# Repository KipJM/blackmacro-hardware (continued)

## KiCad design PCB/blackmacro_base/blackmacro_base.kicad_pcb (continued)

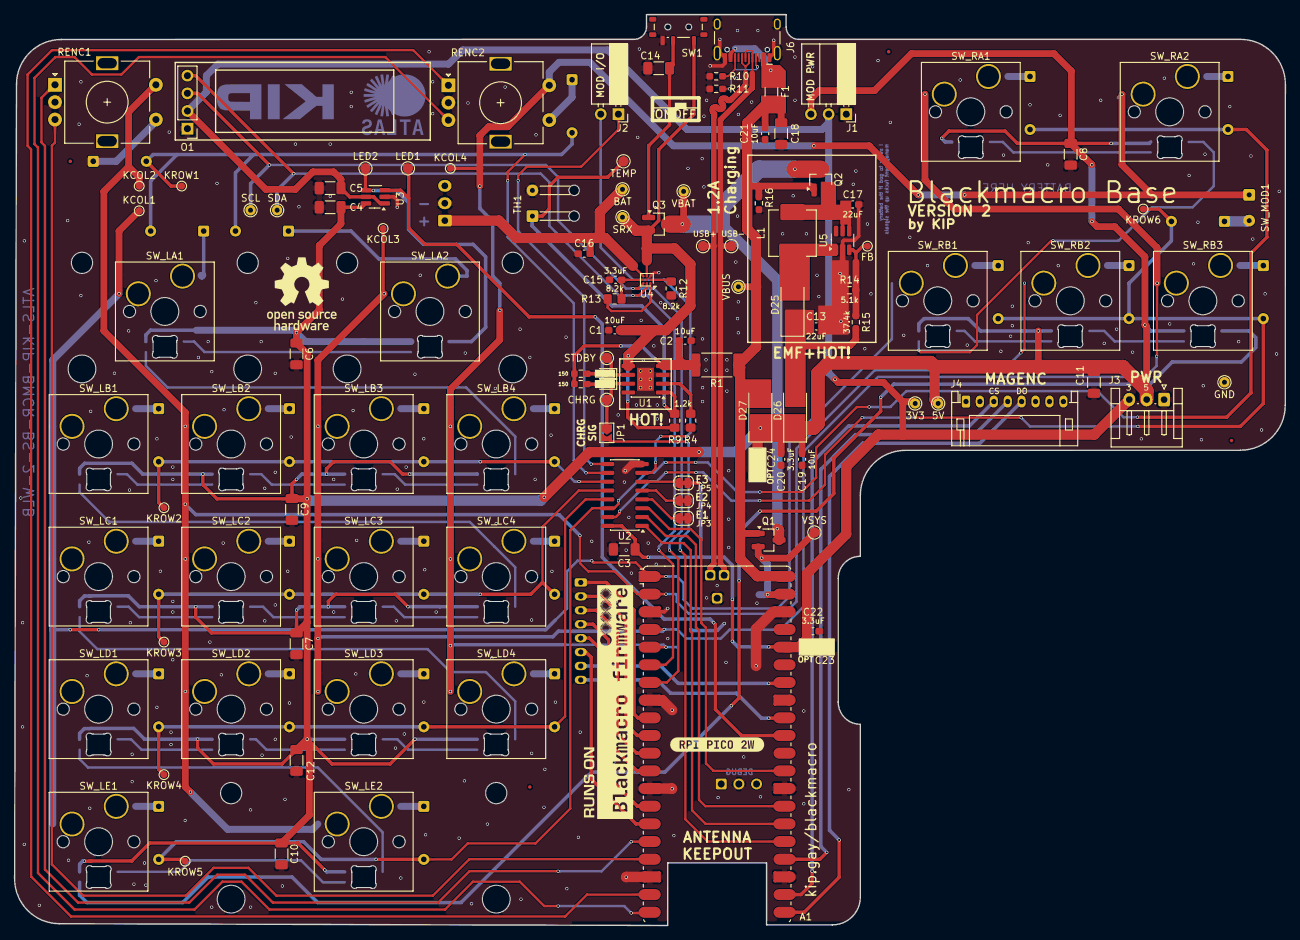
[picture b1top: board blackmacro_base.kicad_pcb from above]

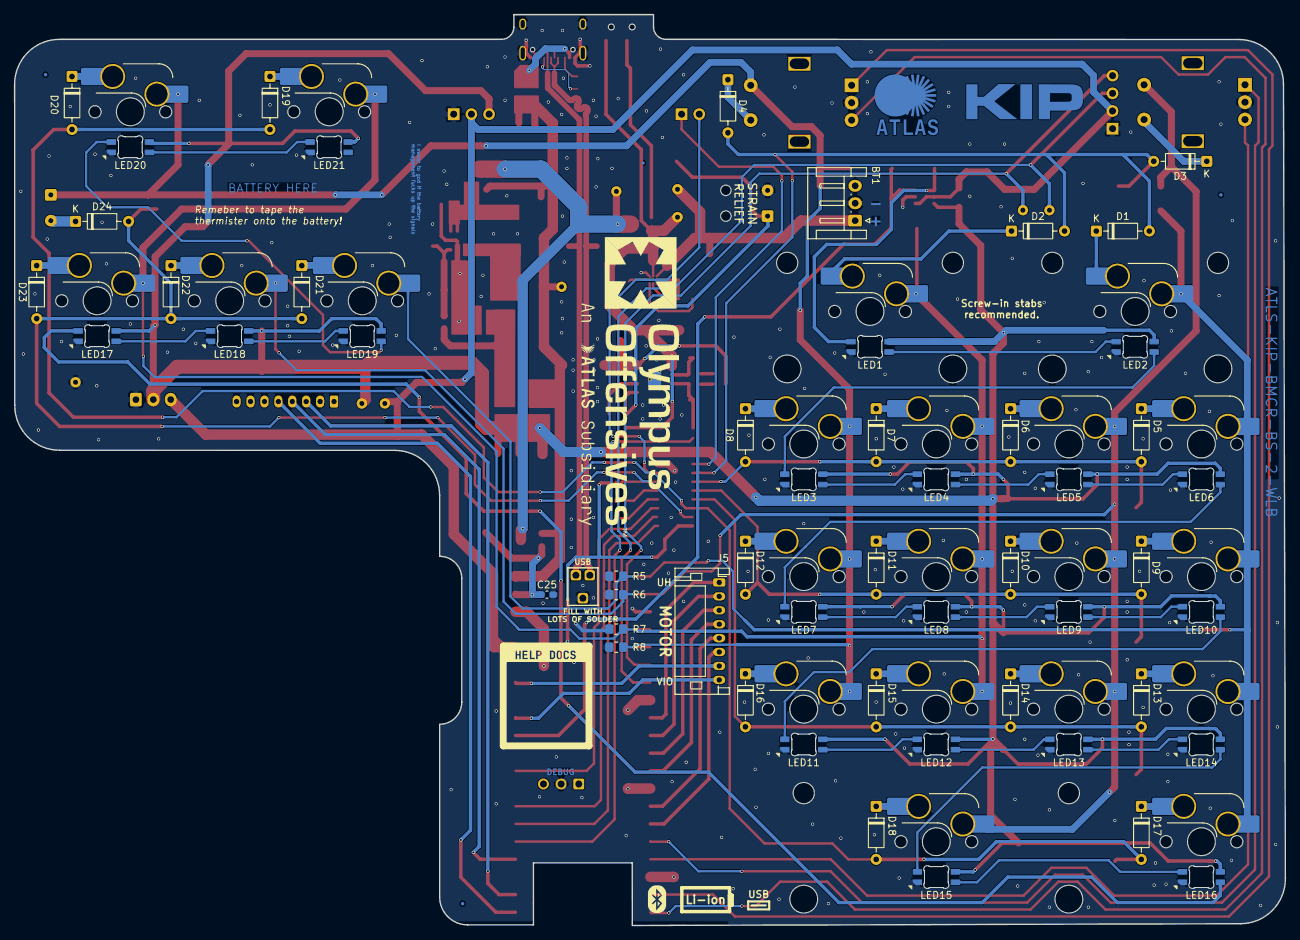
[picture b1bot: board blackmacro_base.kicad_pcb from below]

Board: 2 copper layers, 182.6 x 130.9 mm, 173 parts (53 on the bottom side), 110 nets.

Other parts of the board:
kibuzzard-6A2FA9C2: G***; kibuzzard-6A2FA9C2
kibuzzard-6A574CAA: G***; kibuzzard-6A574CAA

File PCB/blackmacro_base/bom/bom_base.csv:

,References,Value,Footprint,Quantity,Part,Link,Actual Total Cost (CNY)
1,"C3, C4, C5, C6, C7, C8, C9, C10, C11, C12",0.1uF,C_1206_3216Metric_Pad1.33x1.80mm_HandSolder,10,CL31B104KBCNNNC,https://item.szlcsc.com/25237.html,- (SEE DIAL BOM)
2,"R5, R6, R7, R8",8.2k,R_0805_2012Metric_Pad1.20x1.40mm_HandSolder,4,0805W8F8201T5E,https://item.szlcsc.com/18516.html,1.44
3,"D1, D2, D3, D4, D5, D6, D7, D8, D9, D10, D11, D12, D13, D14, D15, D16, D17, D18, D19, D20, D21, D22, D23, D24",1N4148WS,D_DO-35_SOD27_P7.62mm_Horizontal,24,1N4148WS THT,N/A,N/A (from inventory)
4,U2,74HC238,SOIC-16_3.9x9.9mm_P1.27mm,1,"74HC238D,653",https://item.szlcsc.com/6071.html,3.67
5,U3,SN74LVC1T45DBV,SOT-23-6_Handsoldering,1,SN74LVC1T45DBVR,https://item.szlcsc.com/8320.html,2.5
6,A1,RaspberryPi_Pico_W,RaspberryPi_Pico_W_SMD_HandSolder,1,LOBOROBO pico 2W Type-C clone board ,N/A (MUST BE TYPE-C!) (a lot of vendors resell this same exact board),46
7,"LED1, LED2, LED3, LED4, LED5, LED6, LED7, LED8, LED9, LED10, LED11, LED12, LED13, LED14, LED15, LED16, LED17, LED18, LED19, LED20, LED21",SK6812MINI-E,LED_MX_6028R,21,SK6812MINI-E,https://item.szlcsc.com/5773397.html,2.69
8,"SW_LB1, SW_LB2, SW_LB3, SW_LB4, SW_LC1, SW_LC2, SW_LC3, SW_LC4, SW_LD1, SW_LD2, SW_LD3, SW_LD4, SW_LE1, SW_RB1, SW_RB2, SW_RB3",SW_Push_45deg,SW_Hotswap_Kailh_MX_Plated_1.00u,16,CPG151101S11-16,https://item.szlcsc.com/43288200.html,8.22
9,"TP_KCOL1, TP_KCOL2, TP_KCOL3, TP_KCOL4, TP_KROW1, TP_KROW2, TP_KROW3, TP_KROW4, TP_KROW5, TP_KROW6, TP_LED1, TP_LED2",TestPoint,TestPoint_THTPad_D1.5mm_Drill0.7mm,12,N/A,N/A,
10,"TP_3V1, TP_GND1, TP_VBUS1",VSYS test point,TestPoint_THTPad_D1.5mm_Drill0.7mm,3,N/A,N/A,
11,"RENC1, RENC2",RotaryEncoder_Switch,RotaryEncoder_Alps_EC11E-Switch_Vertical_H20mm,2,(from inventory) By personal preference. EC11 rotary encoder with click input,N/A,N/A (from inventory)
12,"ST_LA1, ST_LA2",2u,STAB_MX_2u,2,screw-in 2u stabilizers (very much by your personal preference),Random taobao vendor,16.9
13,"SW_LA1, SW_LA2",SW_Push_45deg,SW_Hotswap_Kailh_MX_Plated_2.00u,2,(SAME AS 1.00u),(SAME AS 1.00u),-
14,"SW_RA1, SW_RA2",SW_Push_45deg,SW_Hotswap_Kailh_MX_Plated_1.50u,2,(SAME AS 1.00u),(SAME AS 1.00u),-
15,O1,OLED_Display,PinHeader_1x04_P2.54mm_Vertical,1,0.91in I2C OLED display module. Pin order must be (top to bottom)  SDA-SCL-VCC-GND,N/A,est. 6.4 (from inventory)
16,ST_LE1,3u,STAB_MX_3u,1,screw-in 3u stabilizers,"stabs from 2u set, wires bought from random vendor",5
17,SW_LE2,SW_Push_45deg,SW_Hotswap_Kailh_MX_Plated_3.00u,1,(SAME AS 1.00u),(SAME AS 1.00u),-
18,SW_MOD1,Conn_01x02_Socket,SolderWire-0.127sqmm_1x02_P3.7mm_D0.48mm_OD1mm,1,N/A,N/A,
19,TP1,SDA,TestPoint_THTPad_D1.5mm_Drill0.7mm,1,N/A,N/A,
20,TP2,SCL,TestPoint_THTPad_D1.5mm_Drill0.7mm,1,N/A,N/A,
21,J1,MOD Power,PinSocket_1x03_P2.54mm_Horizontal,1,NOT POPULATED,NOT POPULATED,
22,J2,MOD I/O,PinSocket_1x03_P2.54mm_Horizontal,1,NOT POPULATED,NOT POPULATED,
23,J3,Dial_PowerConn,JST_EH_S3B-EH_1x03_P2.50mm_Horizontal,1,See dial BOM,See dial BOM,-
24,J4,Dial_MagEncoderConn,JST_PH_S8B-PH-K_1x08_P2.00mm_Horizontal,1,See dial BOM,See dial BOM,-
25,J5,Dial_MotorControlConn,JST_PH_S8B-PH-K_1x08_P2.00mm_Horizontal,1,See dial BOM,See dial BOM,-
26,"extract PCB, glue onto labeled area on PCB",5.1k type-c adapter board,"5.1k Type-C adpater. Should have""5V/5.1K 480Mbps"" printed on metal housing",1,N/A,Random vendor,4.7
27,N/A,Screws,M3*6 flat top hex,12,N/A,Random vendor,1.96
28,N/A,Heat-set Inserts,M3*5mm*4mm,12,N/A,https://www.aliexpress.us/item/2255800046543591.html,3
29,N/A,Key Switches,5-pin Cherry MX-style switch. Preferably translucent / has LED window,21,Gateron KS-3X1 (gateron browns) (very much up to personal preference),random taobao reseller,16.08
30,"SW_LB1, SW_LB2, SW_LB3, SW_LB4, SW_LC1, SW_LC2, SW_LC3, SW_LC4, SW_LD1, SW_LD2, SW_LD3, SW_LD4, SW_LE1, SW_RB1, SW_RB2, SW_RB3",1u Keycaps,1u Keycaps,16,"(from inventory) DSA, up to personal preference",N/A,est. 20 (from inventory)
31,"SW_LA1, SW_LA2",2u keycaps,2u keycaps,2,"DSA, up to personal preference",N/A,18
32,"SW_RA1, SW_RA2",1.5u keycaps,1.5u keycaps,2,"DSA, up to personal preference",N/A,15
33,SW_LE2,3u keycap,3u keycap,1,"XDA, up to personal preference",N/A,8.5
34,N/A,PCB,N/A,1,N/A,N/A,93.9
,,,,,,TOTAL,247.56

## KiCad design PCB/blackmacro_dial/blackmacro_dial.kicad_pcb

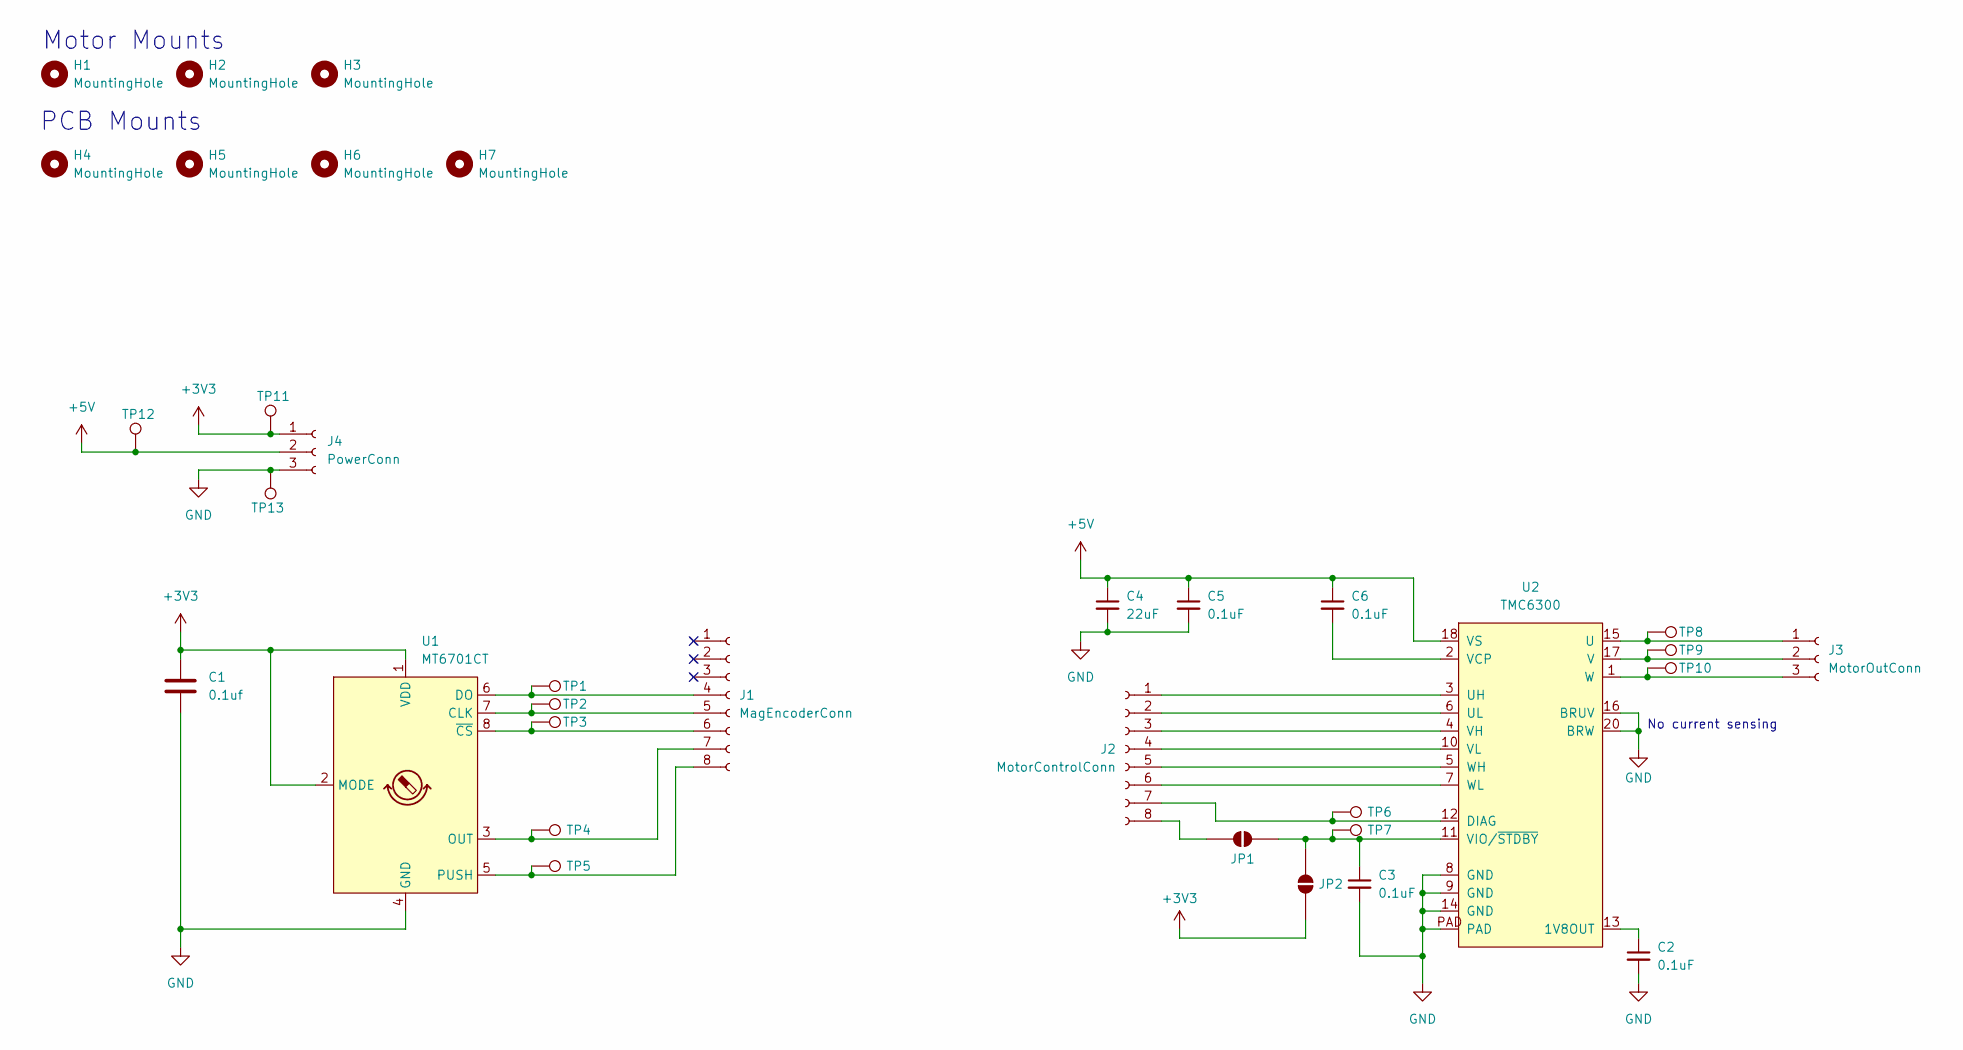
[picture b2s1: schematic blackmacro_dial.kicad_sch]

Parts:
C1: 0.1uf; C_1206_3216Metric_Pad1.33x1.80mm_HandSolder
C2, C3, C5, C6: 0.1uF; C_1206_3216Metric_Pad1.33x1.80mm_HandSolder
C4: 22uF; C_1210_3225Metric_Pad1.33x2.70mm_HandSolder
H1, H2, H3: MountingHole; MountingHole_2.2mm_M2_Pad_TopBottom
H4, H5, H6, H7: MountingHole; MountingHole_2.2mm_M2_Pad
J1: MagEncoderConn; JST_PH_S8B-PH-K_1x08_P2.00mm_Horizontal
J2: MotorControlConn; JST_PH_S8B-PH-K_1x08_P2.00mm_Horizontal; LCSC C20598766
J3: MotorOutConn; JST_EH_S3B-EH_1x03_P2.50mm_Horizontal; LCSC C22382557
J4: PowerConn; JST_EH_S3B-EH_1x03_P2.50mm_Horizontal; LCSC C22382557
JP1: SolderJumper_2_Bridged; SolderJumper-2_P1.3mm_Open_TrianglePad1.0x1.5mm
JP2: SolderJumper_2_Open; SolderJumper-2_P1.3mm_Open_TrianglePad1.0x1.5mm
TP1: MagEnc A; TestPoint_THTPad_D2.0mm_Drill1.0mm
TP2: MagEnc B; TestPoint_THTPad_D2.0mm_Drill1.0mm
TP3: MagEnc Z; TestPoint_THTPad_D2.0mm_Drill1.0mm
TP4: MagEnc Out; TestPoint_THTPad_D2.0mm_Drill1.0mm
TP5: MagEnc Push; TestPoint_THTPad_D2.0mm_Drill1.0mm
TP6: Motor Diagnostics; TestPoint_THTPad_D2.0mm_Drill1.0mm
TP7: Motor VIO; TestPoint_THTPad_D2.0mm_Drill1.0mm
TP8: Motor Out U; TestPoint_THTPad_D2.0mm_Drill1.0mm
TP9: Motor Out V; TestPoint_THTPad_D2.0mm_Drill1.0mm
TP10: Motor Out W; TestPoint_THTPad_D2.0mm_Drill1.0mm
TP11: 3V3; TestPoint_THTPad_D2.0mm_Drill1.0mm
TP12: 5V; TestPoint_THTPad_D2.0mm_Drill1.0mm
TP13: GND; TestPoint_THTPad_D2.0mm_Drill1.0mm
U1: MT6701CT; SO-8_3.9x4.9mm_P1.27mm
U2: TMC6300; QFN-20-1EP_3x3mm_P0.4mm_EP1.65x1.65mm_ThermalVias_LargerVia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

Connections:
+3V3: C1.1, J4.1, JP2.1 (A), TP11.1 (1_1), U1.1 (VDD), U1.2 (MODE)
+5V: C4.1, C5.1, C6.1, J4.2, TP12.1 (1_1), U2.18 (VS)
GND: C1.2, C2.2, C3.2, C4.2, C5.2, J4.3, TP13.1 (1_1), U1.4 (GND), U2.8 (GND), U2.9 (GND), U2.14 (GND), U2.16 (BRUV), U2.20 (BRW), U2.PAD
unnamed: J1.4, TP1.1 (1_1), U1.6 (DO)
unnamed: J1.5, TP2.1 (1_1), U1.7 (CLK)
unnamed: J1.6, TP3.1 (1_1), U1.8 (~CS)
unnamed: J1.7, TP4.1 (1_1), U1.3 (OUT)
unnamed: J1.8, TP5.1 (1_1), U1.5 (PUSH)
unnamed: J2.1, U2.3 (UH)
unnamed: J2.2, U2.6 (UL)
unnamed: J2.3, U2.4 (VH)
unnamed: J2.4, U2.10 (VL)
unnamed: J2.5, U2.5 (WH)
unnamed: J2.6, U2.7 (WL)
unnamed: J2.7, TP6.1 (1_1), U2.12 (DIAG)
unnamed: J2.8, JP1.1 (A)
unnamed: J3.1, TP8.1 (1_1), U2.15 (U)
unnamed: J3.2, TP9.1 (1_1), U2.17 (V)
unnamed: J3.3, TP10.1 (1_1), U2.1 (W)
unnamed: C3.1, JP1.2 (B), JP2.2 (B), TP7.1 (1_1), U2.11 (VIO/~STDBY)
unnamed: C2.1, U2.13 (1V8OUT)
unnamed: C6.2, U2.2 (VCP)

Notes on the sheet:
Motor Mounts
No current sensing
PCB Mounts

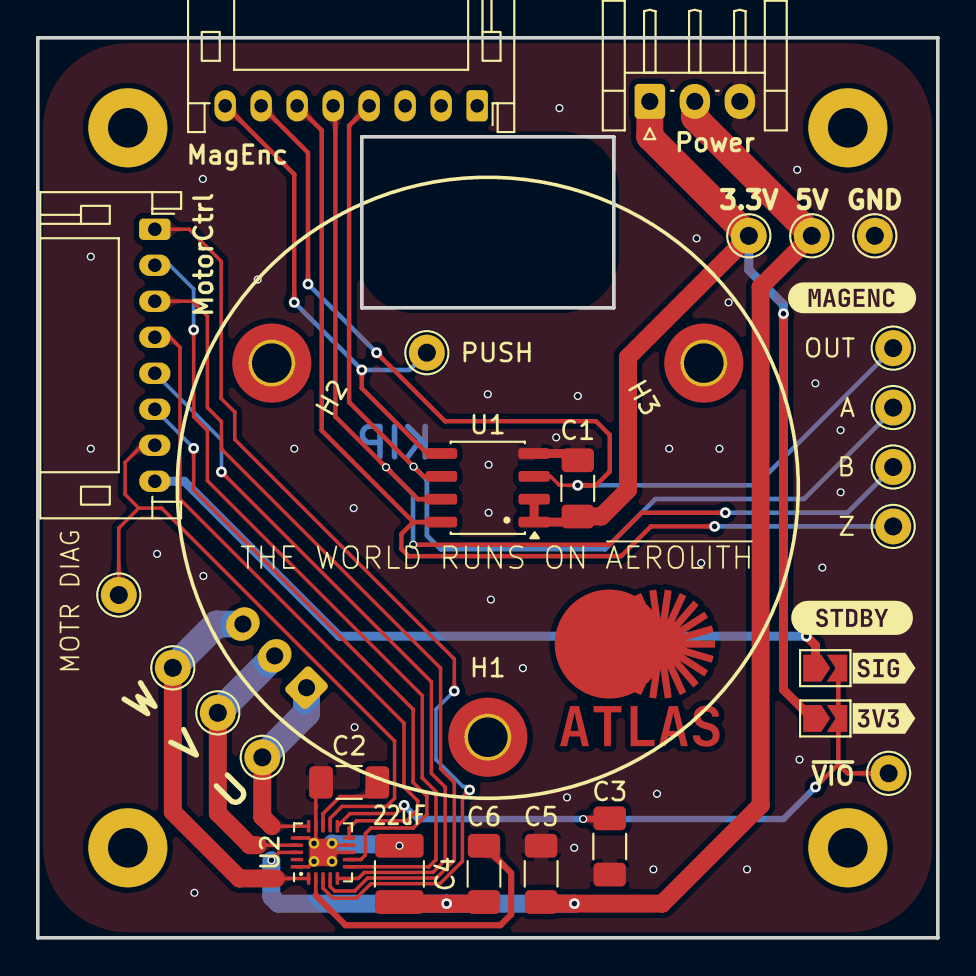
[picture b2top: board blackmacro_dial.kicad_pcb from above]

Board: 2 copper layers, 50.0 x 50.0 mm, 38 parts (1 on the bottom side), 22 nets.

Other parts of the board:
kibuzzard-6A1DA964: G***; kibuzzard-6A1DA964
kibuzzard-6A1DAA49: G***; kibuzzard-6A1DAA49
kibuzzard-6A1DAA68: G***; kibuzzard-6A1DAA68
kibuzzard-6A1DB9AB: G***; kibuzzard-6A1DB9AB

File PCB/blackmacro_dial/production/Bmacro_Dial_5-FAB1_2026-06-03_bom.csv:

Designator,Footprint,Quantity,Value,LCSC Part #
"C1, C2, C3, C5, C6",1206,5,0.1uf,
C4,1210,1,22uF,
J1,JST_PH_S8B-PH-K_1x08_P2.00mm_Horizontal,1,MagEncoderConn,
J2,JST_PH_S8B-PH-K_1x08_P2.00mm_Horizontal,1,MotorControlConn,C20598766
J3,JST_EH_S3B-EH_1x03_P2.50mm_Horizontal,1,MotorOutConn,C22382557
J4,JST_EH_S3B-EH_1x03_P2.50mm_Horizontal,1,PowerConn,C22382557
TP1,TestPoint_THTPad_D2.0mm_Drill1.0mm,1,MagEnc A,
TP10,TestPoint_THTPad_D2.0mm_Drill1.0mm,1,Motor Out W,
TP11,TestPoint_THTPad_D2.0mm_Drill1.0mm,1,3V3,
TP12,TestPoint_THTPad_D2.0mm_Drill1.0mm,1,5V,
TP13,TestPoint_THTPad_D2.0mm_Drill1.0mm,1,GND,
TP2,TestPoint_THTPad_D2.0mm_Drill1.0mm,1,MagEnc B,
TP3,TestPoint_THTPad_D2.0mm_Drill1.0mm,1,MagEnc Z,
TP4,TestPoint_THTPad_D2.0mm_Drill1.0mm,1,MagEnc Out,
TP5,TestPoint_THTPad_D2.0mm_Drill1.0mm,1,MagEnc Push,
TP6,TestPoint_THTPad_D2.0mm_Drill1.0mm,1,Motor Diagnostics,
TP7,TestPoint_THTPad_D2.0mm_Drill1.0mm,1,Motor VIO,
TP8,TestPoint_THTPad_D2.0mm_Drill1.0mm,1,Motor Out U,
TP9,TestPoint_THTPad_D2.0mm_Drill1.0mm,1,Motor Out V,
U1,SO-8_3.9x4.9mm_P1.27mm,1,MT6701CT,
U2,QFN-20-1EP_3x3mm_P0.4mm_EP1.65x1.65mm_ThermalVias_LargerViaHoles,1,TMC6300,

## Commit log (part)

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2026-06-16 fix fix git
2026-06-16 Create LICENSE
2026-06-25 commit before switching to v2
2026-06-25 v1 archive
2026-06-25 v2 switch
2026-06-25 updated pico footprint for pcb usb connections
2026-06-27 switched to pcb usb socket, battery management wip switched to pouch instead of 16850 pcb ready for rewiring + keyboard adjustments
2026-06-28 just the schottky diode left.... the BOM has now grown to 100 cny.... man this thing is gonna be expensive...
